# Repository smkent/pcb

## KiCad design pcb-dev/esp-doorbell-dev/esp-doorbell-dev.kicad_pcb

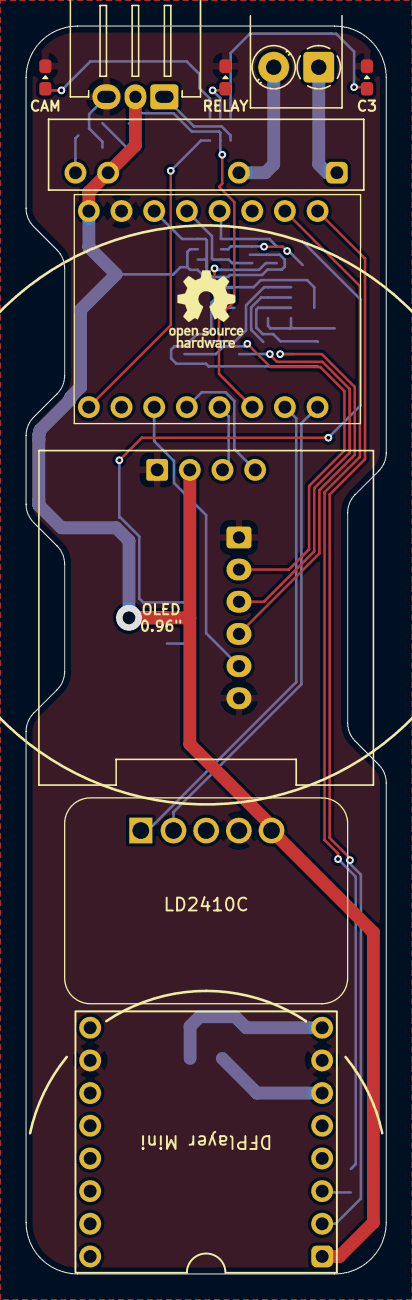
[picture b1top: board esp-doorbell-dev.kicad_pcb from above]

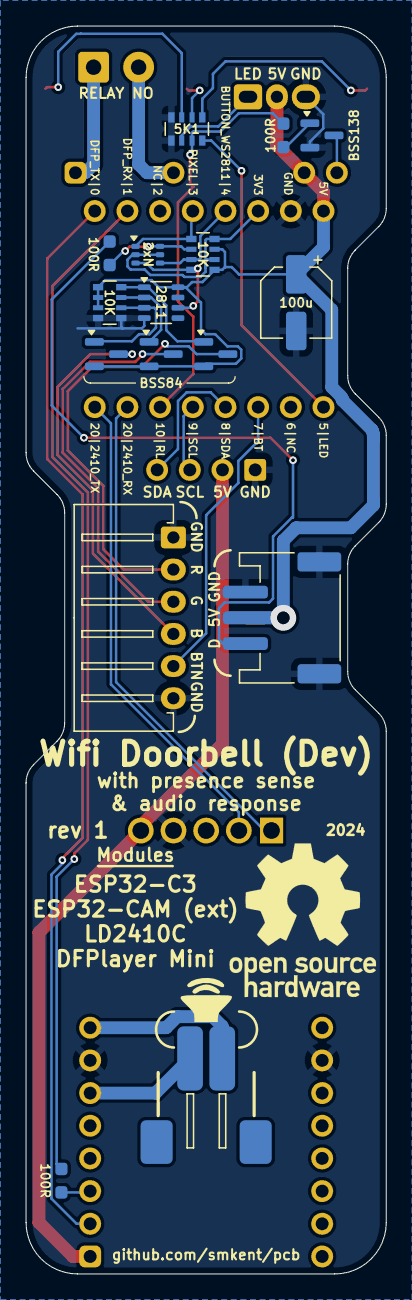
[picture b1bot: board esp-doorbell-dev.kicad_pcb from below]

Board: 2 copper layers, 28.0 x 97.0 mm, 26 parts (16 on the bottom side), 34 nets.

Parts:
C0: 100u; CP_Elec_5x5.4
J1: JST XH; JST_XH_S6B-XH_1x06_P2.50mm_Horizontal
J2: Screw_Terminal_01x02; TerminalBlock_Phoenix_PT-1,5-2-3.5-H_1x02_P3.50mm_Horizonta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
J3: JST XH/PH; Conn_Combo_JST-1x03-XH_PH-THT
J4: JST PH; STEMMA-Signal-SMD-horizontal
LED1, LED2, LED3: LED; LED_0603_1608Metric_Pad1.05x0.95mm_HandSolder_simple
LS1: Speaker; Conn_Combo_JST-1x02-XH_PH-SMD-pad2gnd
Q1, Q2, Q3: BSS84; SOT-23_simple
Q4: 2N7002DW; SOT-363_SC-70-6_simple
Q5: BSS138; SOT-23_simple
R3, R4, R5: 100R; R_0603_1608Metric_Pad0.98x0.95mm_HandSolder_simple
RN1, RN2: 10K; R_Array_Convex_4x0603
RN3: 5K1; R_Array_Convex_4x0603
SM1: ESP32-C3-Super-Mini-Pins
SM2: DFR0299; DFPlayer-Mini-DFR0299-module
SM4: HLK-LD2410C-P; SENSOR-TH_HLK-LD2410C-P
SM5: 0.96mm LCD; LCD-OLED-0.96-module-noholes
U1: WS2811F; FSOP-8_L3.3-W1.7-P0.80-LS2.9-BL
U2: G3MB-202P-5VDC; RELAY-G3MB-202P-5VDC

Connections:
+3V3: Q4.2 (G), Q4.5 (G), RN2.2 (R2.1), RN2.4 (R4.1), SM1.3V3 (+3.3V)
+5V: C0.1, J3.2, J4.2, Q1.2 (S), Q2.2 (S), Q3.2 (S), RN1.1 (R1.1), RN1.2 (R2.1), RN1.3 (R3.1), RN2.1 (R1.1), RN2.3 (R3.1), SM1.5V (+5V), SM2.1 (VCC), SM4.5 (VCC), SM5.2 (VCC), U1.8 (VDD), U2.3
/RELAY_LOW: Q5.3 (D), U2.4
BUTTON: J1.5, SM1.7 (GPIO7/SS)
BUTTON_LED_B: J1.4, Q3.3 (D)
BUTTON_LED_B_EN: Q3.1 (G), RN1.6 (R3.2), U1.3 (OUTB)
BUTTON_LED_G: J1.3, Q2.3 (D)
BUTTON_LED_G_EN: Q2.1 (G), RN1.7 (R2.2), U1.2 (OUTG)
BUTTON_LED_R: J1.2, Q1.3 (D)
BUTTON_LED_R_EN: Q1.1 (G), RN1.8 (R1.2), U1.1 (OUTR)
BUTTON_WS8211: Q4.3 (D), RN2.8 (R1.2), U1.6 (DIN)
BUTTON_WS8211_3V3: Q4.4 (S), RN2.7 (R2.2), SM1.4 (SCK/A4/GPIO4)
C3_LED_STATUS: RN3.8 (R1.2), SM1.5 (GPIO5/A5/MISO)
CAM_LED_STATUS: J3.1, RN3.6 (R3.2)
DOORBELL_RELAY: R5.2, RN3.7 (R2.2), SM1.10 (GPIO10)
GND: C0.2, J1.1, J1.6, J3.3, J4.3, J4.MP (MountPin), LED1.1 (K), LED2.1 (K), LED3.1 (K), Q5.2 (S), RN1.4 (R4.1), RN1.5 (R4.2), RN3.4 (R4.1), RN3.5 (R4.2), SM1.G (GND), SM2.7 (GND), SM2.10 (GND), SM4.4 (GND), SM5.1 (GND), U1.4 (GND)
I2C_SCL: SM1.9 (GPIO9/SCL), SM5.3 (SCL)
I2C_SDA: SM1.8 (GPIO8/SDA), SM5.4 (SDA)
NEOPIXELS: Q4.6 (D), R3.1, RN2.6 (R3.2)
NEOPIXELS_3V3: Q4.1 (S), RN2.5 (R4.2), SM1.3 (A3/GPIO3)
unnamed: J4.1, R3.2
unnamed: LED1.2 (A), RN3.1 (R1.1)
unnamed: LED2.2 (A), RN3.3 (R3.1)
unnamed: LED3.2 (A), RN3.2 (R2.1)
unnamed: Q5.1 (G), R5.1
unnamed: LS1.1, SM2.6 (SPK1)
unnamed: LS1.2, SM2.8 (SPK2)
unnamed: R4.2, SM2.3 (TX)
RELAY_NO_1: J2.1, U2.1
RELAY_NO_2: J2.2, U2.2
UART_1_RX: SM1.20 (GPIO20/RX), SM4.1 (TXD)
UART_1_TX: SM1.21 (GPIO21/TX), SM4.2 (RXD)
UART_2_RX: R4.1, SM1.1 (A1/GPIO1)
UART_2_TX: SM1.0 (A0/GPIO0), SM2.2 (RX)

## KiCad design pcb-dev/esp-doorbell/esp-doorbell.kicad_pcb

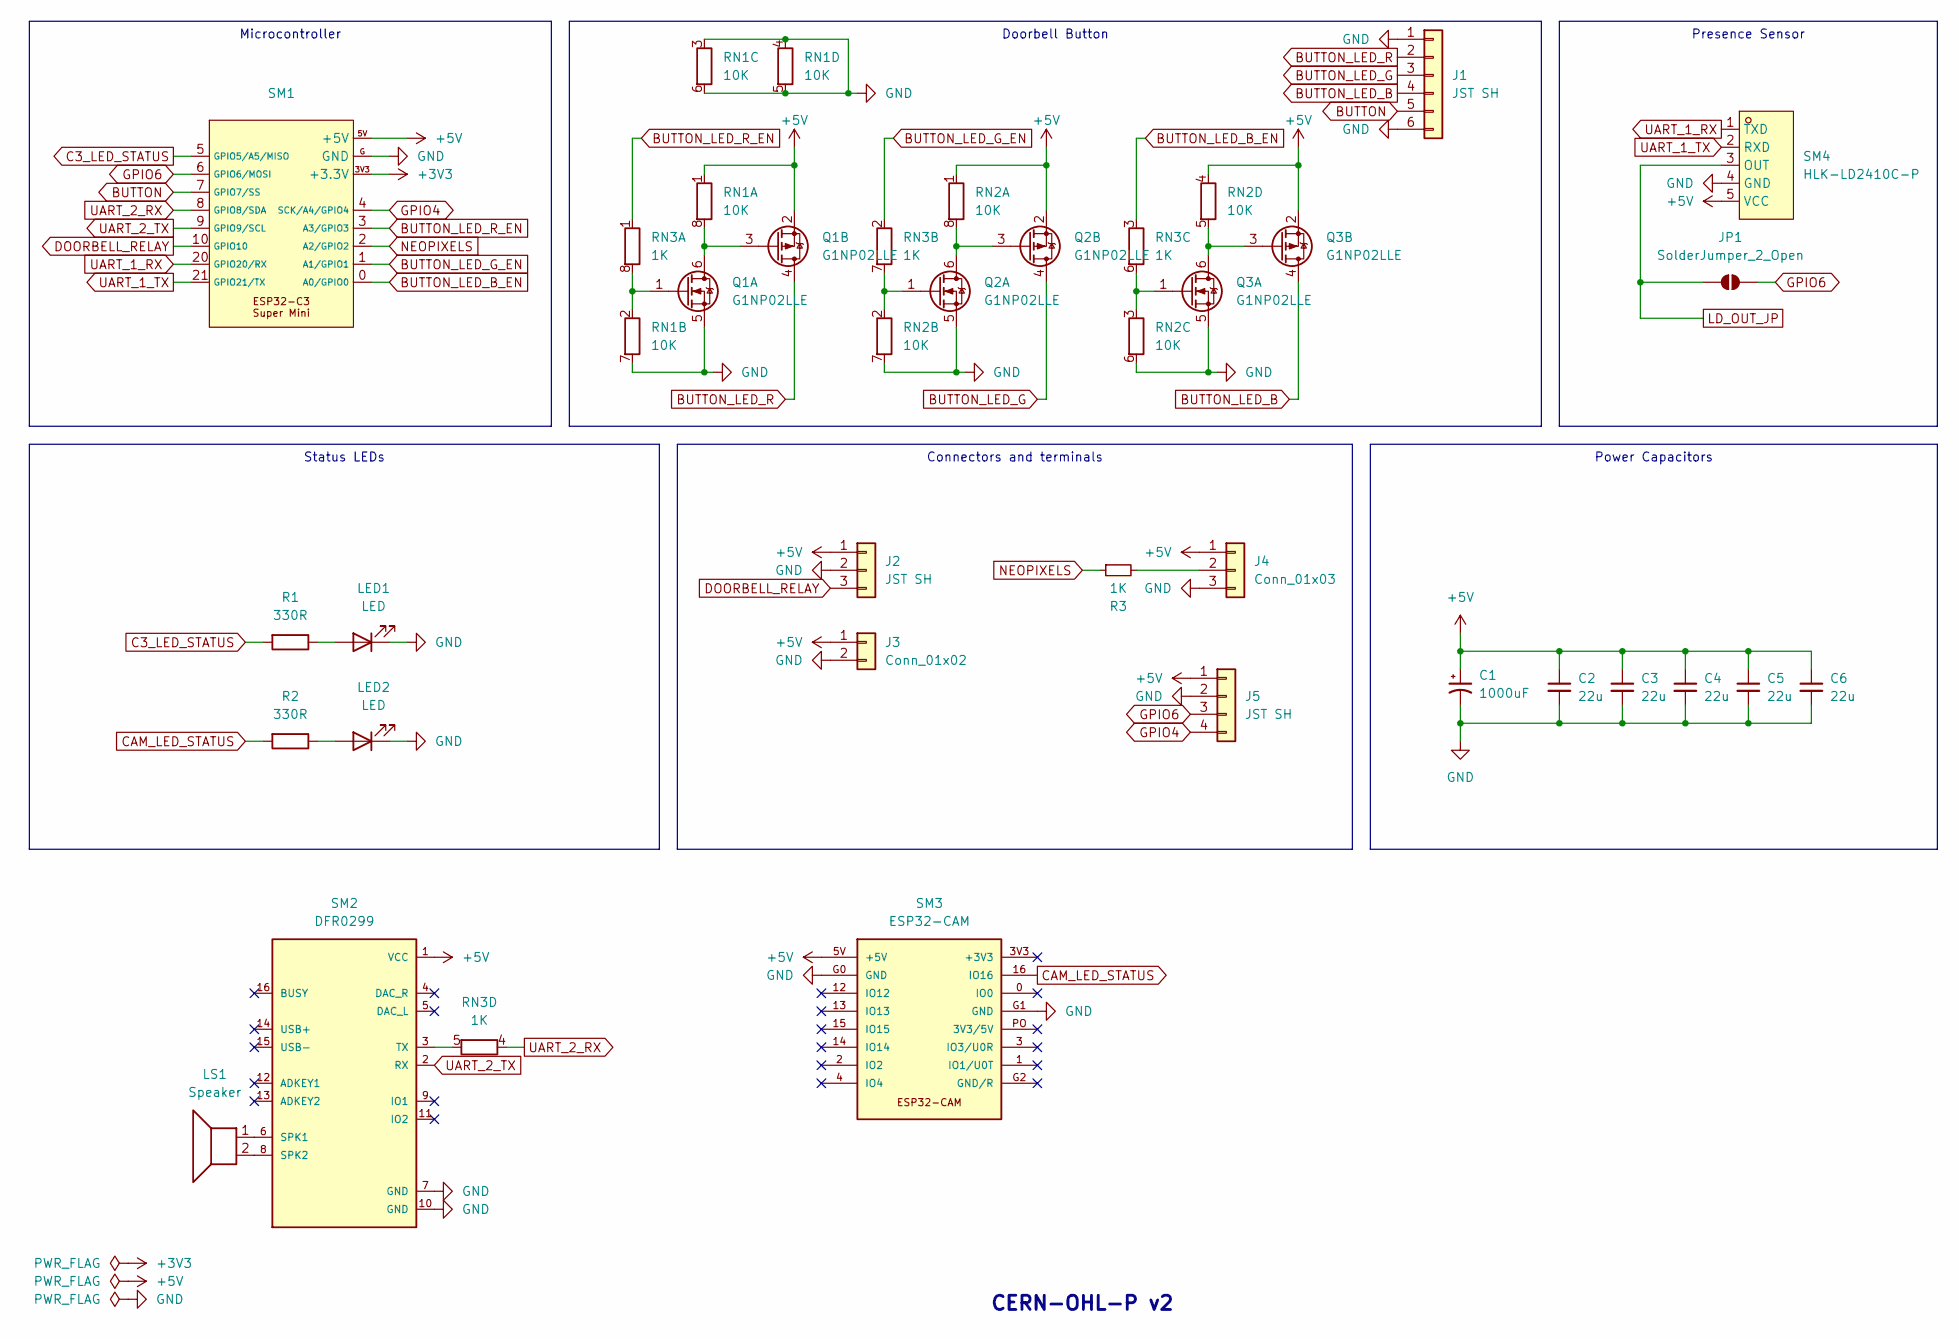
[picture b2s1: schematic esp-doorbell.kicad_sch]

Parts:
C1: 1000uF; CP_Elec_8x10.5
C2, C3, C4, C5, C6: 22u; C_1206_3216Metric_Pad1.33x1.80mm_HandSolder
J1: JST SH; JST_SH_SM06B-SRSS-TB_1x06-1MP_P1.00mm_Horizontal
J2: JST SH; JST_SH_SM03B-SRSS-TB_1x03-1MP_P1.00mm_Horizontal
J3: Conn_01x02; JST_XH_S2B-XH_1x02_P2.50mm_Horizontal
J4: Conn_01x03; JST_XH_S3B-XH_1x03_P2.50mm_Horizontal_pad2gnd
J5: JST SH; JST_SH_SM04B-SRSS-TB_1x04-1MP_P1.00mm_Horizontal
JP1: SolderJumper_2_Open; SolderJumper-2_P1.3mm_Open_TrianglePad1.0x1.5mm
LED1, LED2: LED; LED_0603_1608Metric_Pad1.05x0.95mm_HandSolder_simple
LS1: Speaker; JST_SH_SM02B-SRSS-TB_1x02-1MP_P1.00mm_Horizontal
Q1, Q2, Q3: G1NP02LLE; SOT-23-6; LCSC Part C7465318
R1, R2: 330R; R_0805_2012Metric_Pad1.20x1.40mm_HandSolder
R3: 1K; R_0805_2012Metric_Pad1.20x1.40mm_HandSolder
RN1, RN2: 10K; R_Array_Convex_4x0603
RN3: 1K; R_Array_Convex_4x0603
SM1: ESP32-C3-Super-Mini-Castellated-SMD
SM2: DFR0299; DFPlayer-Mini-DFR0299-module
SM3: ESP32-CAM
SM4: HLK-LD2410C-P; SENSOR-TH_HLK-LD2410C-P; LCSC Part C19723500

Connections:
+3V3: SM1.3V3 (+3.3V)
+5V: C1.1, C2.1, C3.1, C4.1, C5.1, C6.1, J2.1, J3.1, J4.1, J5.1, Q1.2 (S), Q2.2 (S), Q3.2 (S), RN1.1 (R1.1), RN2.1 (R1.1), RN2.4 (R4.1), SM1.5V (+5V), SM2.1 (VCC), SM3.5V (+5V), SM4.5 (VCC)
BUTTON: J1.5, SM1.7 (GPIO7/SS)
BUTTON_LED_B: J1.4, Q3.4 (D)
BUTTON_LED_B_EN: RN3.3 (R3.1), SM1.0 (A0/GPIO0)
BUTTON_LED_G: J1.3, Q2.4 (D)
BUTTON_LED_G_EN: RN3.2 (R2.1), SM1.1 (A1/GPIO1)
BUTTON_LED_R: J1.2, Q1.4 (D)
BUTTON_LED_R_EN: RN3.1 (R1.1), SM1.3 (A3/GPIO3)
C3_LED_STATUS: R1.2, SM1.5 (GPIO5/A5/MISO)
CAM_LED_STATUS: R2.2, SM3.16 (IO16)
DOORBELL_RELAY: J2.3, SM1.10 (GPIO10)
GND: C1.2, C2.2, C3.2, C4.2, C5.2, C6.2, J1.1, J1.6, J2.2, J3.2, J4.3, J5.2, LED1.1 (K), LED2.1 (K), Q1.5 (S), Q2.5 (S), Q3.5 (S), RN1.3 (R3.1), RN1.4 (R4.1), RN1.5 (R4.2), RN1.6 (R3.2), RN1.7 (R2.2), RN2.6 (R3.2), RN2.7 (R2.2), SM1.G (GND), SM2.7 (GND), SM2.10 (GND), SM3.G0 (GND), SM3.G1 (GND), SM4.4 (GND)
GPIO4: J5.4, SM1.4 (SCK/A4/GPIO4)
GPIO6: J5.3, JP1.2 (B), SM1.6 (GPIO6/MOSI)
LD_OUT_JP: JP1.1 (A), SM4.3 (OUT)
NEOPIXELS: R3.1, SM1.2 (A2/GPIO2)
unnamed: J4.2, R3.2
unnamed: LED1.2 (A), R1.1
unnamed: LED2.2 (A), R2.1
unnamed: Q1.3 (G), Q1.6 (D), RN1.8 (R1.2)
unnamed: Q1.1 (G), RN1.2 (R2.1), RN3.8 (R1.2)
unnamed: Q2.3 (G), Q2.6 (D), RN2.8 (R1.2)
unnamed: Q2.1 (G), RN2.2 (R2.1), RN3.7 (R2.2)
unnamed: Q3.3 (G), Q3.6 (D), RN2.5 (R4.2)
unnamed: Q3.1 (G), RN2.3 (R3.1), RN3.6 (R3.2)
unnamed: RN3.5 (R4.2), SM2.3 (TX)
unnamed: LS1.1, SM2.6 (SPK1)
unnamed: LS1.2, SM2.8 (SPK2)
UART_1_RX: SM1.20 (GPIO20/RX), SM4.1 (TXD)
UART_1_TX: SM1.21 (GPIO21/TX), SM4.2 (RXD)
UART_2_RX: RN3.4 (R4.1), SM1.8 (GPIO8/SDA)
UART_2_TX: SM1.9 (GPIO9/SCL), SM2.2 (RX)

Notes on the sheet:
Microcontroller
Doorbell Button
Presence Sensor
Status LEDs
Power Capacitors
Connectors and terminals
CERN-OHL-P v2

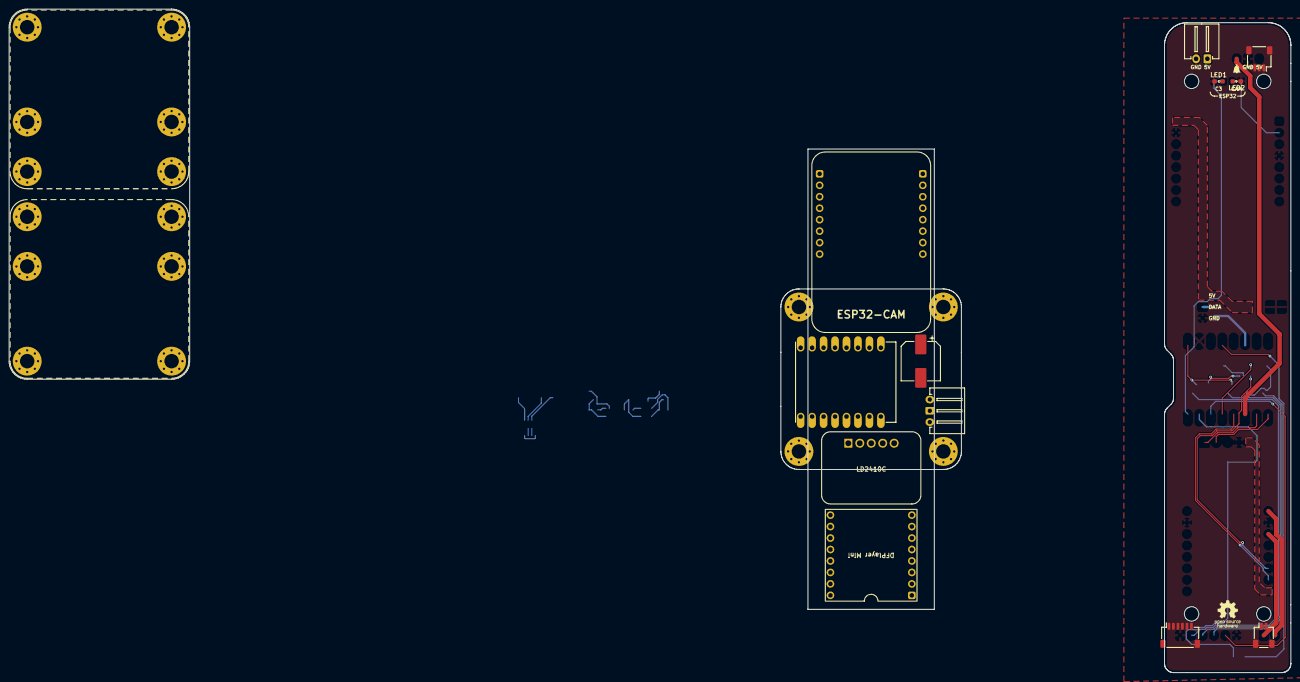
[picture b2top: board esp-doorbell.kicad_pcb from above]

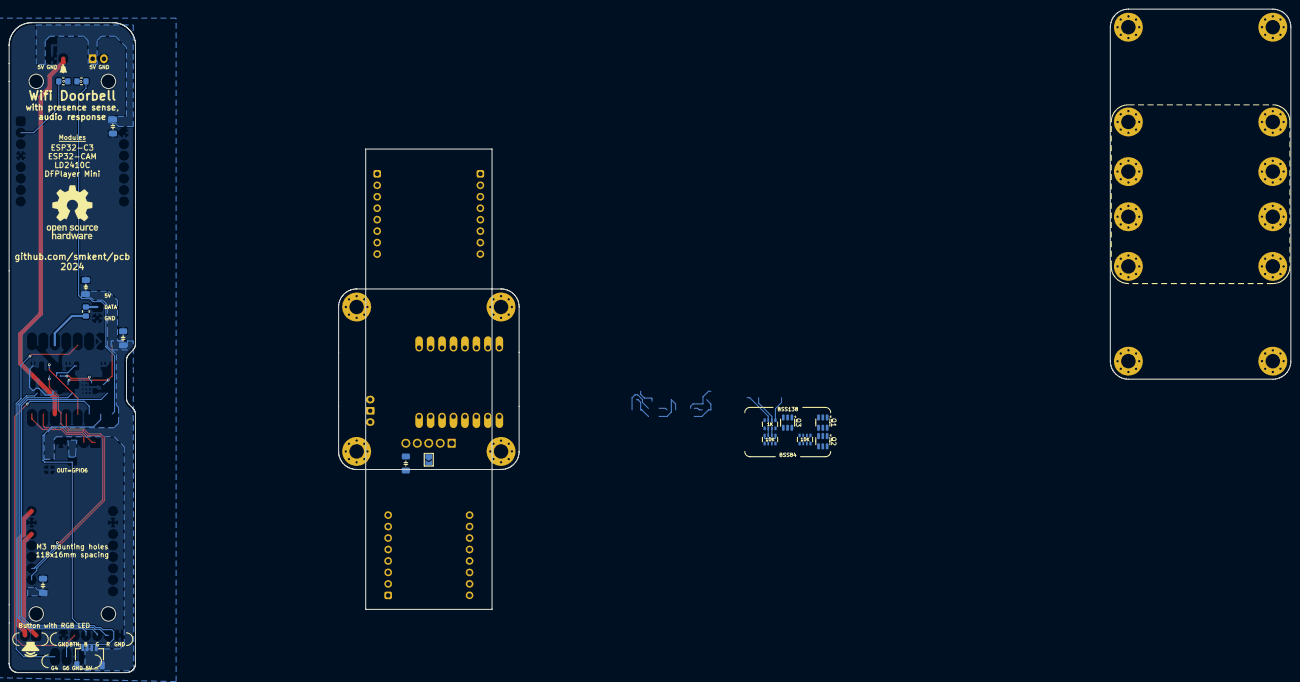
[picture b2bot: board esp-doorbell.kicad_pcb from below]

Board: 2 copper layers, 284.0 x 147.0 mm, 28 parts (16 on the bottom side), 32 nets.

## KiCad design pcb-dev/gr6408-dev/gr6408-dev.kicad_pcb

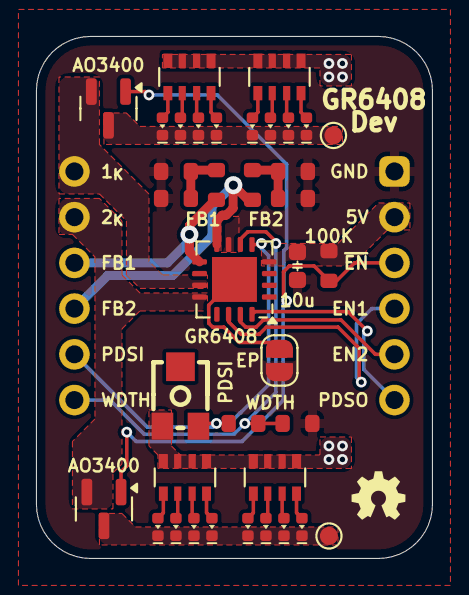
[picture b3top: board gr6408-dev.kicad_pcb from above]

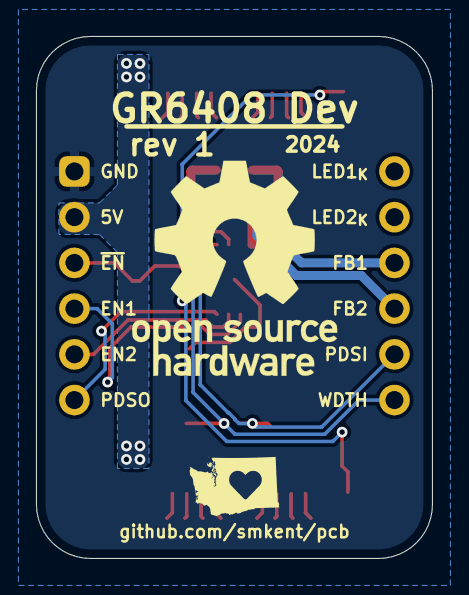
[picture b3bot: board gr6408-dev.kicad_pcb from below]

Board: 2 copper layers, 22.0 x 29.0 mm, 39 parts (2 on the bottom side), 33 nets.

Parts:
C1: 10u; C_0603_1608Metric
J1: Pin headers; PinHeader_1x06_P2.54mm_Vertical_simple_pad1gnd
J2: Pin headers; PinHeader_1x06_P2.54mm_Vertical_simple
JP1: SolderJumper_2_Open; SolderJumper-2_P1.3mm_Open_RoundedPad1.0x1.5mm
LED1, LED2, LED3, LED4, LED5, LED6, LED7, LED8, LED9, LED10, LED11, LED12, LED13, LED14, LED15, LED16: LED_Small; LED_0402_1005Metric
Q1, Q2: AO3400A; SOT-23
R1, R2, R3, R4, R5, R6: 1R; R_0603_1608Metric_simple
R7: 100K; R_0603_1608Metric_simple
R8: 2M; R_0603_1608Metric_simple
R9: 510K; R_0603_1608Metric_simple
RN1, RN2, RN3, RN4: 1K; R_Array_Convex_4x0603
RV1: 500K; RES-ADJ-SMD_VG039NCH
TP1, TP2: TestPoint; TestPoint_Pad_D1.0mm
U1: GR6408; QFN-16-1EP_4x4mm_P0.65mm_EP2.5x2.5mm

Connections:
+5V: C1.1, J1.2, R7.1, RN1.5 (R4.2), RN1.6 (R3.2), RN1.7 (R2.2), RN1.8 (R1.2), RN2.5 (R4.2), RN2.6 (R3.2), RN2.7 (R2.2), RN2.8 (R1.2), RN3.5 (R4.2), RN3.6 (R3.2), RN3.7 (R2.2), RN3.8 (R1.2), RN4.5 (R4.2), RN4.6 (R3.2), RN4.7 (R2.2), RN4.8 (R1.2), RV1.1, U1.4 (VCC)
/LED1_K_PRE: LED1.1 (K), LED2.1 (K), LED3.1 (K), LED4.1 (K), LED5.1 (K), LED6.1 (K), LED7.1 (K), LED8.1 (K), Q1.3 (D), TP1.1
/LED2_K_PRE: LED9.1 (K), LED10.1 (K), LED11.1 (K), LED12.1 (K), LED13.1 (K), LED14.1 (K), LED15.1 (K), LED16.1 (K), Q2.3 (D), TP2.1
EN1: J1.4, U1.14 (EN1)
EN2: J1.5, U1.15 (EN2)
FB1: J2.3, R1.1, U1.9 (FB1)
FB2: J2.4, R4.1, U1.8 (FB2)
GND: C1.2, J1.1, JP1.1 (A), R2.2, R3.2, R5.2, R6.2, R9.2, U1.7 (GND)
LED1_K: J2.1, Q1.2 (S), U1.11 (LED1-)
LED2_K: J2.2, Q2.2 (S), U1.12 (LED2-)
unnamed: JP1.2 (B), U1.17 (EP)
unnamed: LED1.2 (A), RN1.1 (R1.1)
unnamed: LED2.2 (A), RN1.2 (R2.1)
unnamed: LED3.2 (A), RN1.3 (R3.1)
unnamed: LED4.2 (A), RN1.4 (R4.1)
unnamed: LED5.2 (A), RN2.1 (R1.1)
unnamed: LED6.2 (A), RN2.2 (R2.1)
unnamed: LED7.2 (A), RN2.3 (R3.1)
unnamed: LED8.2 (A), RN2.4 (R4.1)
unnamed: LED9.2 (A), RN3.1 (R1.1)
unnamed: LED10.2 (A), RN3.2 (R2.1)
unnamed: LED11.2 (A), RN3.3 (R3.1)
unnamed: LED12.2 (A), RN3.4 (R4.1)
unnamed: LED13.2 (A), RN4.1 (R1.1)
unnamed: LED14.2 (A), RN4.2 (R2.1)
unnamed: LED15.2 (A), RN4.3 (R3.1)
unnamed: LED16.2 (A), RN4.4 (R4.1)
unnamed: R1.2, R2.1, R3.1
unnamed: R4.2, R5.1, R6.1
ONBOARD_LED_EN: J1.3, Q1.1 (G), Q2.1 (G), R7.2
PDSI: J2.5, R8.1, RV1.3, U1.5 (PDSI)
PDSO: J1.6, U1.16 (PDSO)
WIDTH: J2.6, R8.2, R9.1, U1.6 (WIDTH)

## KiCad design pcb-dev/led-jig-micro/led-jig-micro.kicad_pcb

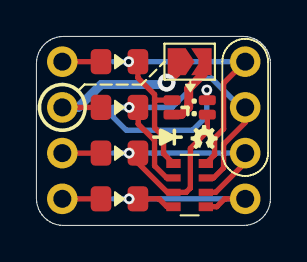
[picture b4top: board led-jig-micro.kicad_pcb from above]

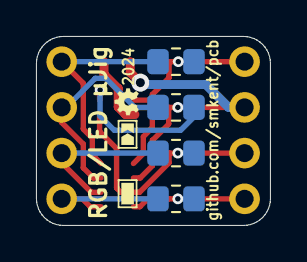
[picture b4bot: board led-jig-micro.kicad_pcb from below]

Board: 2 copper layers, 13.0 x 10.5 mm, 13 parts (6 on the bottom side), 13 nets.

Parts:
J1, J2: Conn_01x04; PinHeader_1x04_P2.54mm_Vertical_simple
JP1: SolderJumper_2_Open; SolderJumper-2_P1.3mm_Open_TrianglePad1.0x1.5mm
LED0: LED_RGAB; LED-ARRAY-SMD_4P-L2.0-W1.3-BR_HandSolder
LED1, LED2, LED3, LED4: LED; LED_0805_2012Metric_Pad1.15x1.40mm_HandSolder_simple
R1, R2, R3, R4: R; R_0805_2012Metric_Pad1.20x1.40mm_HandSolder
RN1: R; R_Array_Convex_4x0603

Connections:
LED1_ANODE: J2.1, LED1.2 (A)
LED1_CATHODE: J1.1, R1.2, RN1.8 (R1.2)
LED1_RESISTOR: LED0.1 (RK), LED1.1 (K), R1.1, RN1.1 (R1.1)
LED2_ANODE: J2.2, JP1.1 (A), LED2.2 (A)
LED2_CATHODE: J1.2, R2.2, RN1.7 (R2.2)
LED2_RESISTOR: LED0.2 (GK), LED2.1 (K), R2.1, RN1.2 (R2.1)
LED3_ANODE: J2.3, LED3.2 (A)
LED3_CATHODE: J1.3, R3.2, RN1.6 (R3.2)
LED3_RESISTOR: LED0.4 (BK), LED3.1 (K), R3.1, RN1.3 (R3.1)
LED4_ANODE: J2.4, LED4.2 (A)
LED4_CATHODE: J1.4, R4.2, RN1.5 (R4.2)
unnamed: JP1.2 (B), LED0.3 (A)
unnamed: LED4.1 (K), R4.1, RN1.4 (R4.1)

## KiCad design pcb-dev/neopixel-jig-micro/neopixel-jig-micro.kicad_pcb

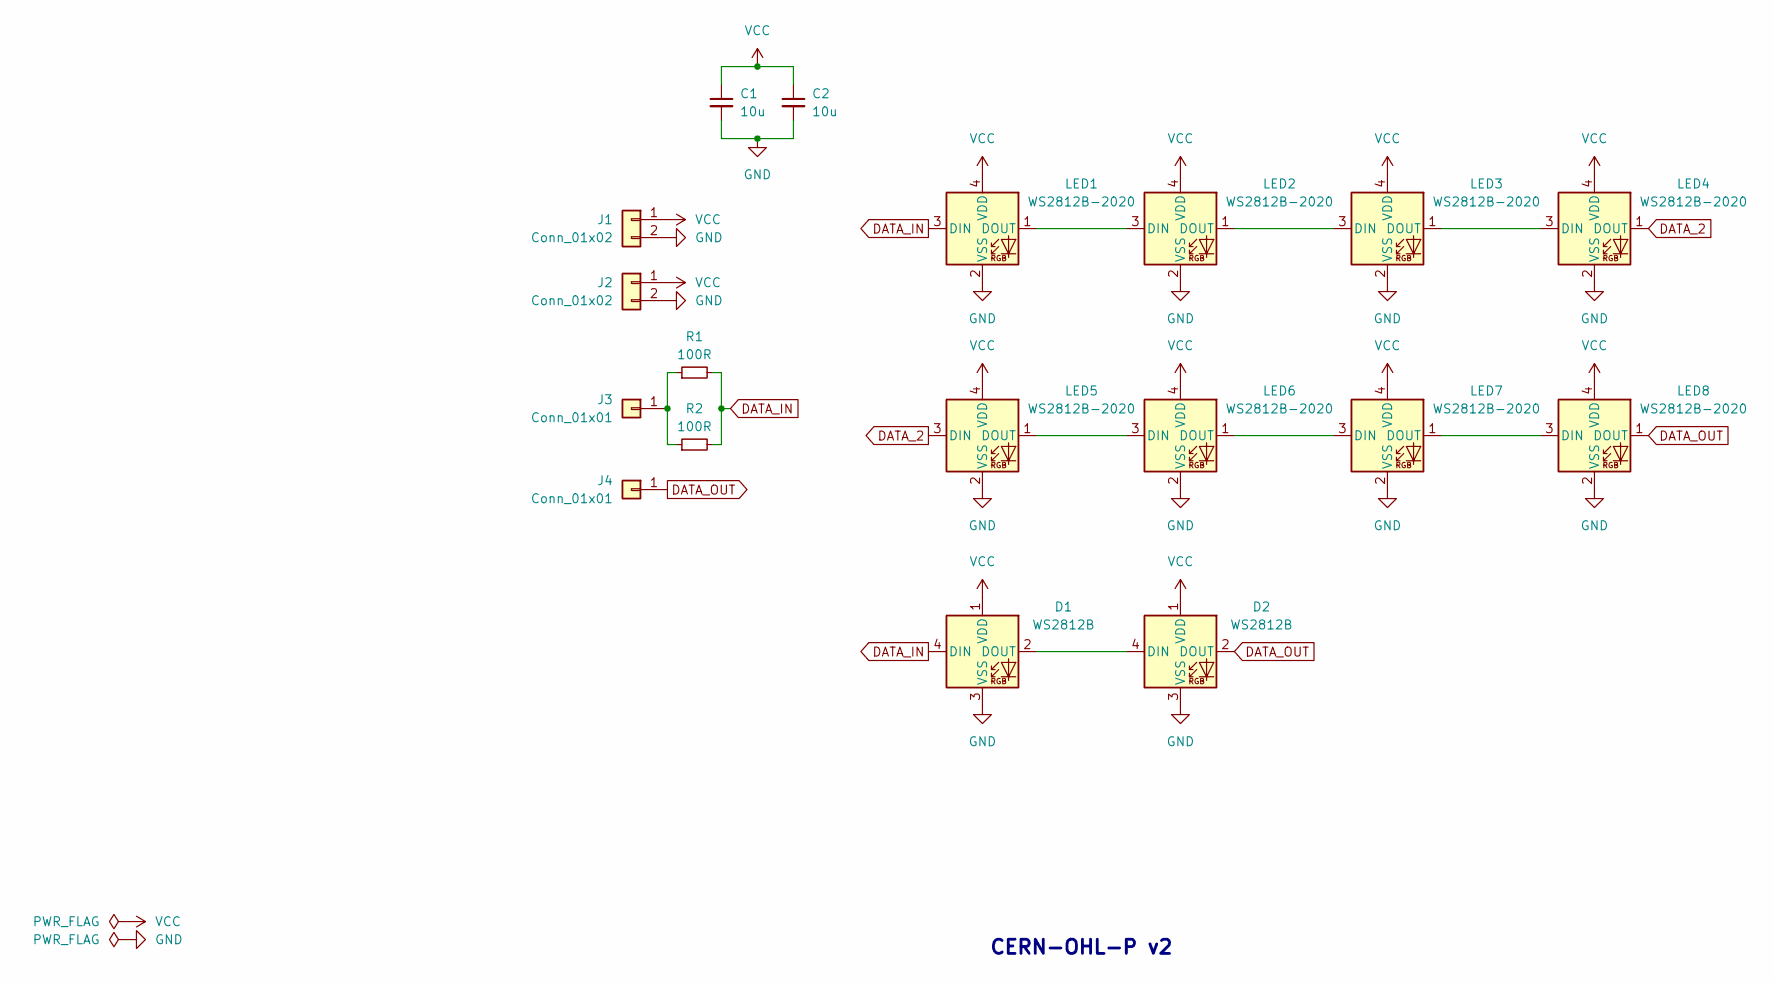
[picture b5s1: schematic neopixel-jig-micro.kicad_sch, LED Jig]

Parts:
C1, C2: 10u; C_0603_1608Metric_Pad1.08x0.95mm_HandSolder
D1, D2: WS2812B; LED_WS2812B_PLCC4_5.0x5.0mm_P3.2mm_simple_small_courtyard
J1, J2: Conn_01x02; PinHeader_1x02_P2.54mm_Vertical_simple
J3, J4: Conn_01x01; PinHeader_1x01_P2.54mm_simple
LED1, LED2, LED3, LED4, LED5, LED6, LED7, LED8: WS2812B-2020; LED-SMD_4P-L2.0-W2.0-BR-1
R1, R2: 100R; R_0603_1608Metric_Pad0.98x0.95mm_HandSolder

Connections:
DATA_2: LED4.1 (DOUT), LED5.3 (DIN)
DATA_IN: D1.4 (DIN), LED1.3 (DIN), R1.2, R2.2
DATA_OUT: D2.2 (DOUT), J4.1, LED8.1 (DOUT)
GND: C1.2, C2.2, D1.3 (VSS), D2.3 (VSS), J1.2, J2.2, LED1.2 (VSS), LED2.2 (VSS), LED3.2 (VSS), LED4.2 (VSS), LED5.2 (VSS), LED6.2 (VSS), LED7.2 (VSS), LED8.2 (VSS)
unnamed: D1.2 (DOUT), D2.4 (DIN)
unnamed: J3.1, R1.1, R2.1
unnamed: LED1.1 (DOUT), LED2.3 (DIN)
unnamed: LED2.1 (DOUT), LED3.3 (DIN)
unnamed: LED3.1 (DOUT), LED4.3 (DIN)
unnamed: LED5.1 (DOUT), LED6.3 (DIN)
unnamed: LED6.1 (DOUT), LED7.3 (DIN)
unnamed: LED7.1 (DOUT), LED8.3 (DIN)
VCC: C1.1, C2.1, D1.1 (VDD), D2.1 (VDD), J1.1, J2.1, LED1.4 (VDD), LED2.4 (VDD), LED3.4 (VDD), LED4.4 (VDD), LED5.4 (VDD), LED6.4 (VDD), LED7.4 (VDD), LED8.4 (VDD)

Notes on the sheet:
CERN-OHL-P v2

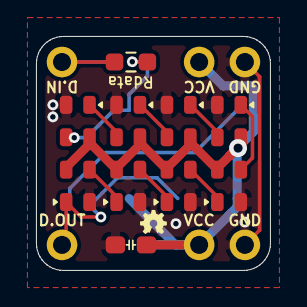
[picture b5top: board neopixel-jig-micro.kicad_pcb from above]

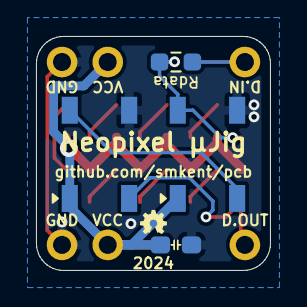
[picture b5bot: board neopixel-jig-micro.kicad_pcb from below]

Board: 2 copper layers, 13.0 x 13.0 mm, 18 parts (8 on the bottom side), 13 nets.

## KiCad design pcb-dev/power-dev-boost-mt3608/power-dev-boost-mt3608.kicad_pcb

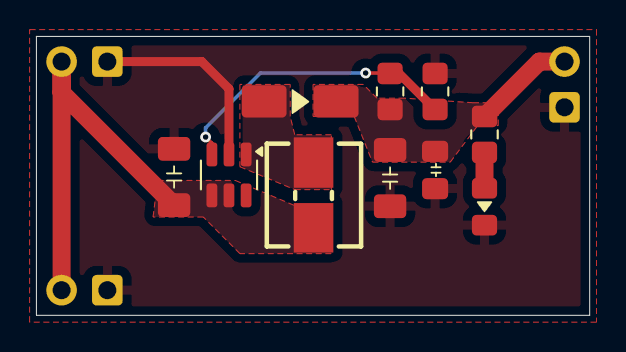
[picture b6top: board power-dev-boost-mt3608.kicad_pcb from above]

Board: 2 copper layers, 30.7 x 15.5 mm, 13 parts (0 on the bottom side), 6 nets.

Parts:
C1: 22uF; C_1206_3216Metric_Pad1.33x1.80mm_HandSolder
C2: 22uf; C_1206_3216Metric_Pad1.33x1.80mm_HandSolder
C3: 10uF; C_0805_2012Metric_Pad1.18x1.45mm_HandSolder
D1: SS34; D_SMA_simple
J1, J2, J3: Conn_01x02; PinHeader_1x02_P2.54mm_Vertical_simple_pad2gnd
L1: 22uH; Inductor_Multi_5.2x5.7_2x2.5
LED1: Boost; LED_0805_2012Metric_Pad1.15x1.40mm_HandSolder_simple
R1: 75K; R_0805_2012Metric_Pad1.20x1.40mm_HandSolder
R2, R3: 10K; R_0805_2012Metric_Pad1.20x1.40mm_HandSolder
U1: MT3608; SOT-23-6

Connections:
FB: R1.2, R2.1, U1.3 (FB)
GND: C1.2, C2.2, C3.2, J1.2, J2.2, J3.2, LED1.1 (K), R2.2, U1.2 (GND)
unnamed: LED1.2 (A), R3.2
SW: D1.2 (A), L1.2, U1.1 (SW)
VCC: C1.1, J1.1, J2.1, L1.1, U1.4 (EN), U1.5 (IN)
VOUT: C2.1, C3.1, D1.1 (K), J3.1, R1.1, R3.1

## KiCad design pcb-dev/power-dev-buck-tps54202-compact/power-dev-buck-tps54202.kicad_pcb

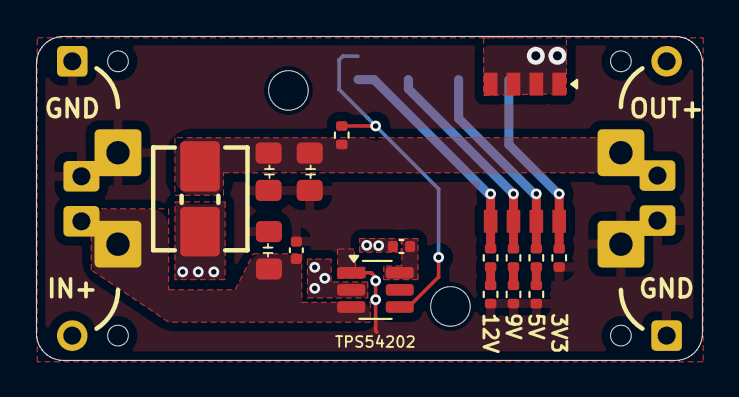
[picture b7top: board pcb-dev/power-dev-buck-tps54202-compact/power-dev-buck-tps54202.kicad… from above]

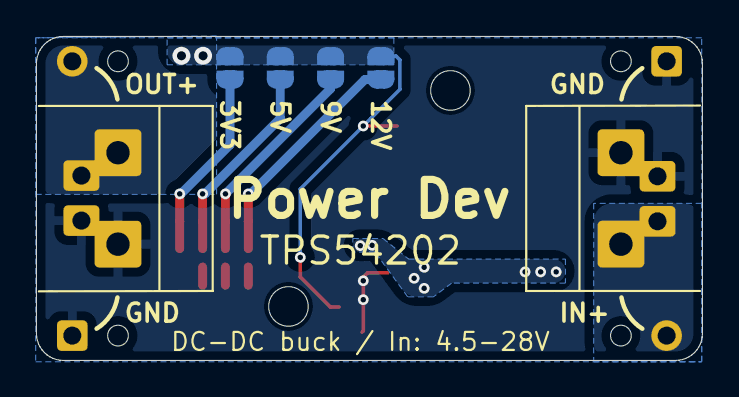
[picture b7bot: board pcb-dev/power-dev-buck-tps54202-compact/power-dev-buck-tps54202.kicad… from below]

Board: 2 copper layers, 37.0 x 18.0 mm, 26 parts (10 on the bottom side), 13 nets.

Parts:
C1: 10u; C_0805_2012Metric_Pad1.18x1.45mm_HandSolder
C2, C3: 0u1; C_0402_1005Metric
C4, C5: 22u; C_0805_2012Metric_Pad1.18x1.45mm_HandSolder
J1, J3: Conn_01x03; PinHeader_1x01_P2.54mm_simple
J2, J4: Conn_01x03; PinHeader_1x01_P2.54mm_simple_square
J5, J6: Screw_Terminal_01x02; TerminalBlock_or_JST_2.54_1x02
JP1, JP2, JP3, JP4: SolderJumper_2_Open; SolderJumper-2_P1.3mm_Open_RoundedPad1.0x1.5mm_simple
L1: 15u; Inductor_Multi_5.2x5.7_2x2.5
R1: 100K; R_0402_1005Metric
R2: 22K; R_0402_1005Metric
R3: 12K; R_0402_1005Metric
R4: 1K2; R_0402_1005Metric
R5: 6.8K; R_0402_1005Metric
R6: 220R; R_0402_1005Metric
R7: 5.1K; R_0402_1005Metric
R8: 120R; R_0402_1005Metric
SW1: SW_DIP_x04; SW_DIP_SPSTx04_Slide_P1.27mm_simple
U1: TPS54202DDCR; SOT-23-6_Handsoldering

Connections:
3V3_SELECT: JP1.1 (A), R2.1, SW1.8
5V_SELECT: JP2.1 (A), R3.1, SW1.7
9V_SELECT: JP3.1 (A), R5.1, SW1.6
12V_SELECT: JP4.1 (A), R7.1, SW1.5
BOOT: C3.1, U1.6 (BOOT)
FB: JP1.2 (B), JP2.2 (B), JP3.2 (B), JP4.2 (B), R1.2, SW1.1, SW1.2, SW1.3, SW1.4, U1.4 (FB)
GND: C1.2, C2.2, C4.2, C5.2, J2.1, J4.1, J5.2, J6.2, R2.2, R4.2, R6.2, R8.2, U1.1 (GND)
unnamed: R3.2, R4.1
unnamed: R5.2, R6.1
unnamed: R7.2, R8.1
SW: C3.2, L1.1, U1.2 (SW)
VIN: C1.1, C2.1, J1.1, J5.1, U1.3 (VIN)
VOUT: C4.1, C5.1, J3.1, J6.1, L1.2, R1.1

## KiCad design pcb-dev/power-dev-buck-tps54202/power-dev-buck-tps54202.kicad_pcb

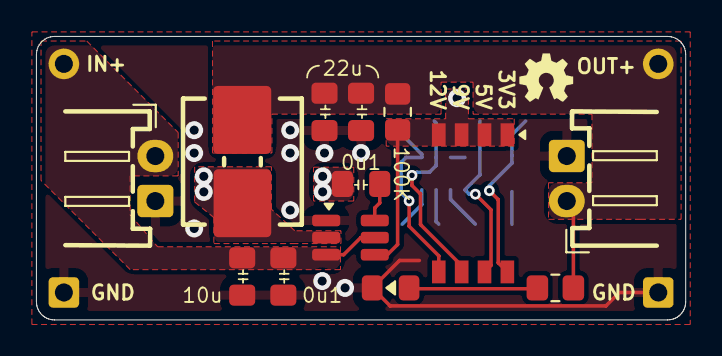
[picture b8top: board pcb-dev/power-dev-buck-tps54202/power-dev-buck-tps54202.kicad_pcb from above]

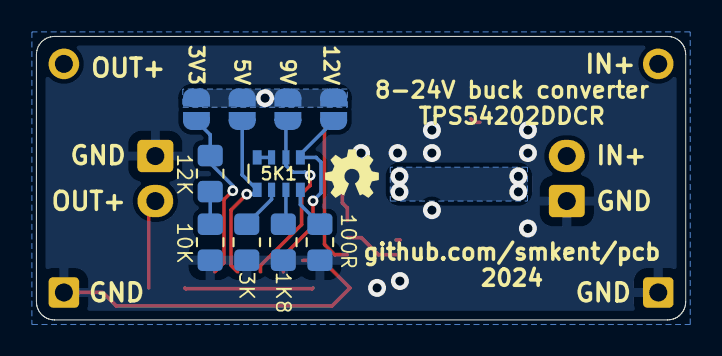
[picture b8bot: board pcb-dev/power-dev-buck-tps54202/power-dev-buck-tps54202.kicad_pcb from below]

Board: 2 copper layers, 36.1 x 15.7 mm, 27 parts (14 on the bottom side), 16 nets.

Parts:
C1: 10u; C_0805_2012Metric_Pad1.18x1.45mm_HandSolder
C2, C3: 0u1; C_0805_2012Metric_Pad1.18x1.45mm_HandSolder
C4, C5: 22u; C_0805_2012Metric_Pad1.18x1.45mm_HandSolder
D1: LED; LED_0805_2012Metric_Pad1.15x1.40mm_HandSolder_simple
J1, J3: Conn_01x03; PinHeader_1x01_P2.54mm_simple
J2, J4: Conn_01x03; PinHeader_1x01_P2.54mm_simple_square
J5, J6: Conn_01x02; JST_XH_S2B-XH-2AW_1x02_P2.50mm_pad2gnd_trim2
JP1, JP2, JP3, JP4: SolderJumper_2_Open; SolderJumper-2_P1.3mm_Open_RoundedPad1.0x1.5mm_simple
L1: 15u; Inductor_Multi_7.0x6.6_plus
R0: 100K; R_0805_2012Metric_Pad1.20x1.40mm_HandSolder
R1: 10K; R_0805_2012Metric_Pad1.20x1.40mm_HandSolder
R2: 12K; R_0805_2012Metric_Pad1.20x1.40mm_HandSolder
R4: 3K; R_0805_2012Metric_Pad1.20x1.40mm_HandSolder
R6: 1K8; R_0805_2012Metric_Pad1.20x1.40mm_HandSolder
R8: 100R; R_0805_2012Metric_Pad1.20x1.40mm_HandSolder
R10: 1K; R_0805_2012Metric_Pad1.20x1.40mm_HandSolder
RN1: 5K1; R_Array_Convex_4x0603
SW1: SW_DIP_x04; SW_DIP_SPSTx04_Slide_P1.27mm_simple
U1: TPS54202DDCR; SOT-23-6_Handsoldering_simple

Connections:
3V3_SELECT: JP1.1 (A), R2.1, SW1.8
5V_SELECT: JP2.1 (A), RN1.5 (R4.2), SW1.7
9V_SELECT: JP3.1 (A), RN1.2 (R2.1), SW1.6
12V_SELECT: JP4.1 (A), RN1.1 (R1.1), SW1.5
BOOT: C3.1, U1.6 (BOOT)
FB: JP1.2 (B), JP2.2 (B), JP3.2 (B), JP4.2 (B), R0.2, SW1.1, SW1.2, SW1.3, SW1.4, U1.4 (FB)
GND: C1.2, C2.2, C4.2, C5.2, D1.1 (K), J2.1, J4.1, J5.2, J6.2, R1.2, R4.2, R6.2, R8.2, U1.1 (GND)
unnamed: D1.2 (A), R10.2
unnamed: R1.1, R2.2
unnamed: R8.1, RN1.8 (R1.2)
unnamed: R6.1, RN1.7 (R2.2)
unnamed: RN1.3 (R3.1), RN1.4 (R4.1)
unnamed: R4.1, RN1.6 (R3.2)
SW: C3.2, L1.1, U1.2 (SW)
VIN: C1.1, C2.1, J1.1, J5.1, U1.3 (VIN), U1.5 (EN)
VOUT: C4.1, C5.1, J3.1, J6.1, L1.2, R0.1, R10.1
